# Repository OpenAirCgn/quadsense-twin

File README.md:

# quadsense-twin

This repository contains schematics and board files for an OpenAir
module intended to evaluate the viability of an alternative circuitry to
Alphasense provided ISB (individual support board) for gas sensors.

The board design is based on the original quadsense, with two ISB
mounted sensors replaced by sensors mounted directly on the board. The
support circuitry provided by the ISB boards is integrated directly on
the board.

# Circuitry

Each sensor has four electrodes. The circuit to the left of the sensor
maintains a constant voltage at the counter and reference electrodes.
The circuitry to the right of the electrodes amplifies and filters the
current flowing from the working and auxiliary electrodes.

The concentration being measured is proportional to the difference of
the working electrode exposed to the gas and the unexposed auxiliary
electrode.

The voltage maintained at the referenced and counter electrodes may be offset
by a bias voltage. 

Whether a positive or negative bias voltage is applied voltage
determined by jumper configuration (U1: R16/R17 & R18/R19, U2: R20/R21 &
R22/R23). The value of the bias is determined by a voltage divider (U1:
R12/R13, U2:R14/R15). 

The photograph below highlights an unbiased (U2, top rectangle) and 200mV biased
configuration (U1, bottom rectangle, R12=15k R13=12k). 

# Test boards

| MAC | Sensor U1 | Sensor U2 | ISB 1 | ISB 2 |
|-|-|-|-|-|
| 30:AE:A4:0A:AA:98 | [C0-B4](http://www.alphasense.com/WEB1213/wp-content/uploads/2019/09/CO-B4.pdf) | [OX-B431](http://www.alphasense.com/WEB1213/wp-content/uploads/2019/09/OX-B431.pdf) | CO-B4 | OX-B431 |
| 30:AE:A4:0A:A9:D8 | [NO-B4](http://www.alphasense.com/WEB1213/wp-content/uploads/2019/09/NO-B4.pdf) (biased) | [NO2-B43F](http://www.alphasense.com/WEB1213/wp-content/uploads/2019/09/NO2-B43F.pdf) | NO-B4 | NO2-B43F |

# Sensor Configuration

The following picture and table describe the sensor configuration:

| Name Schematic | ADC Channel | Tag Firehose | Name Firehose | Sensor AA:98 | Sensor A9:D8 |
| -- | - | - | - | - | - |
| U1 | 2 | 0x03 | OA_Alpha_3 | CO-B4 working electrode   | NO-B4 working |
| U1 | 3 | 0x04 | OA_Alpha_4 | CO-B4 auxiliary electrode | NO-B4 AUX |
| U2 | 0 | 0x01 | OA_Alpha_1 | OX-B431 working           | NO2-B43F working |
| U2 | 1 | 0x02 | OA_Alpha_2 | OX-B431 AUX               | NO2-B43F AUX |
| P3 | 4 | 0x05 | OA_Alpha_5 | CO-B4 (ISB) working       | NO-B4 (ISB) working |
| P3 | 5 | 0x06 | OA_Alpha_6 | CO-B4 (ISB) AUX           | NO-B4 (ISB) AUX |
| P4 | 6 | 0x07 | OA_Alpha_7 | OX-B431 (ISB) working     | NO2-B43F (ISB) working |
| P4 | 7 | 0x08 | OA_Alpha_8 | OX-B431 (ISB) AUX         | NO2-B43F (ISB) AUX |

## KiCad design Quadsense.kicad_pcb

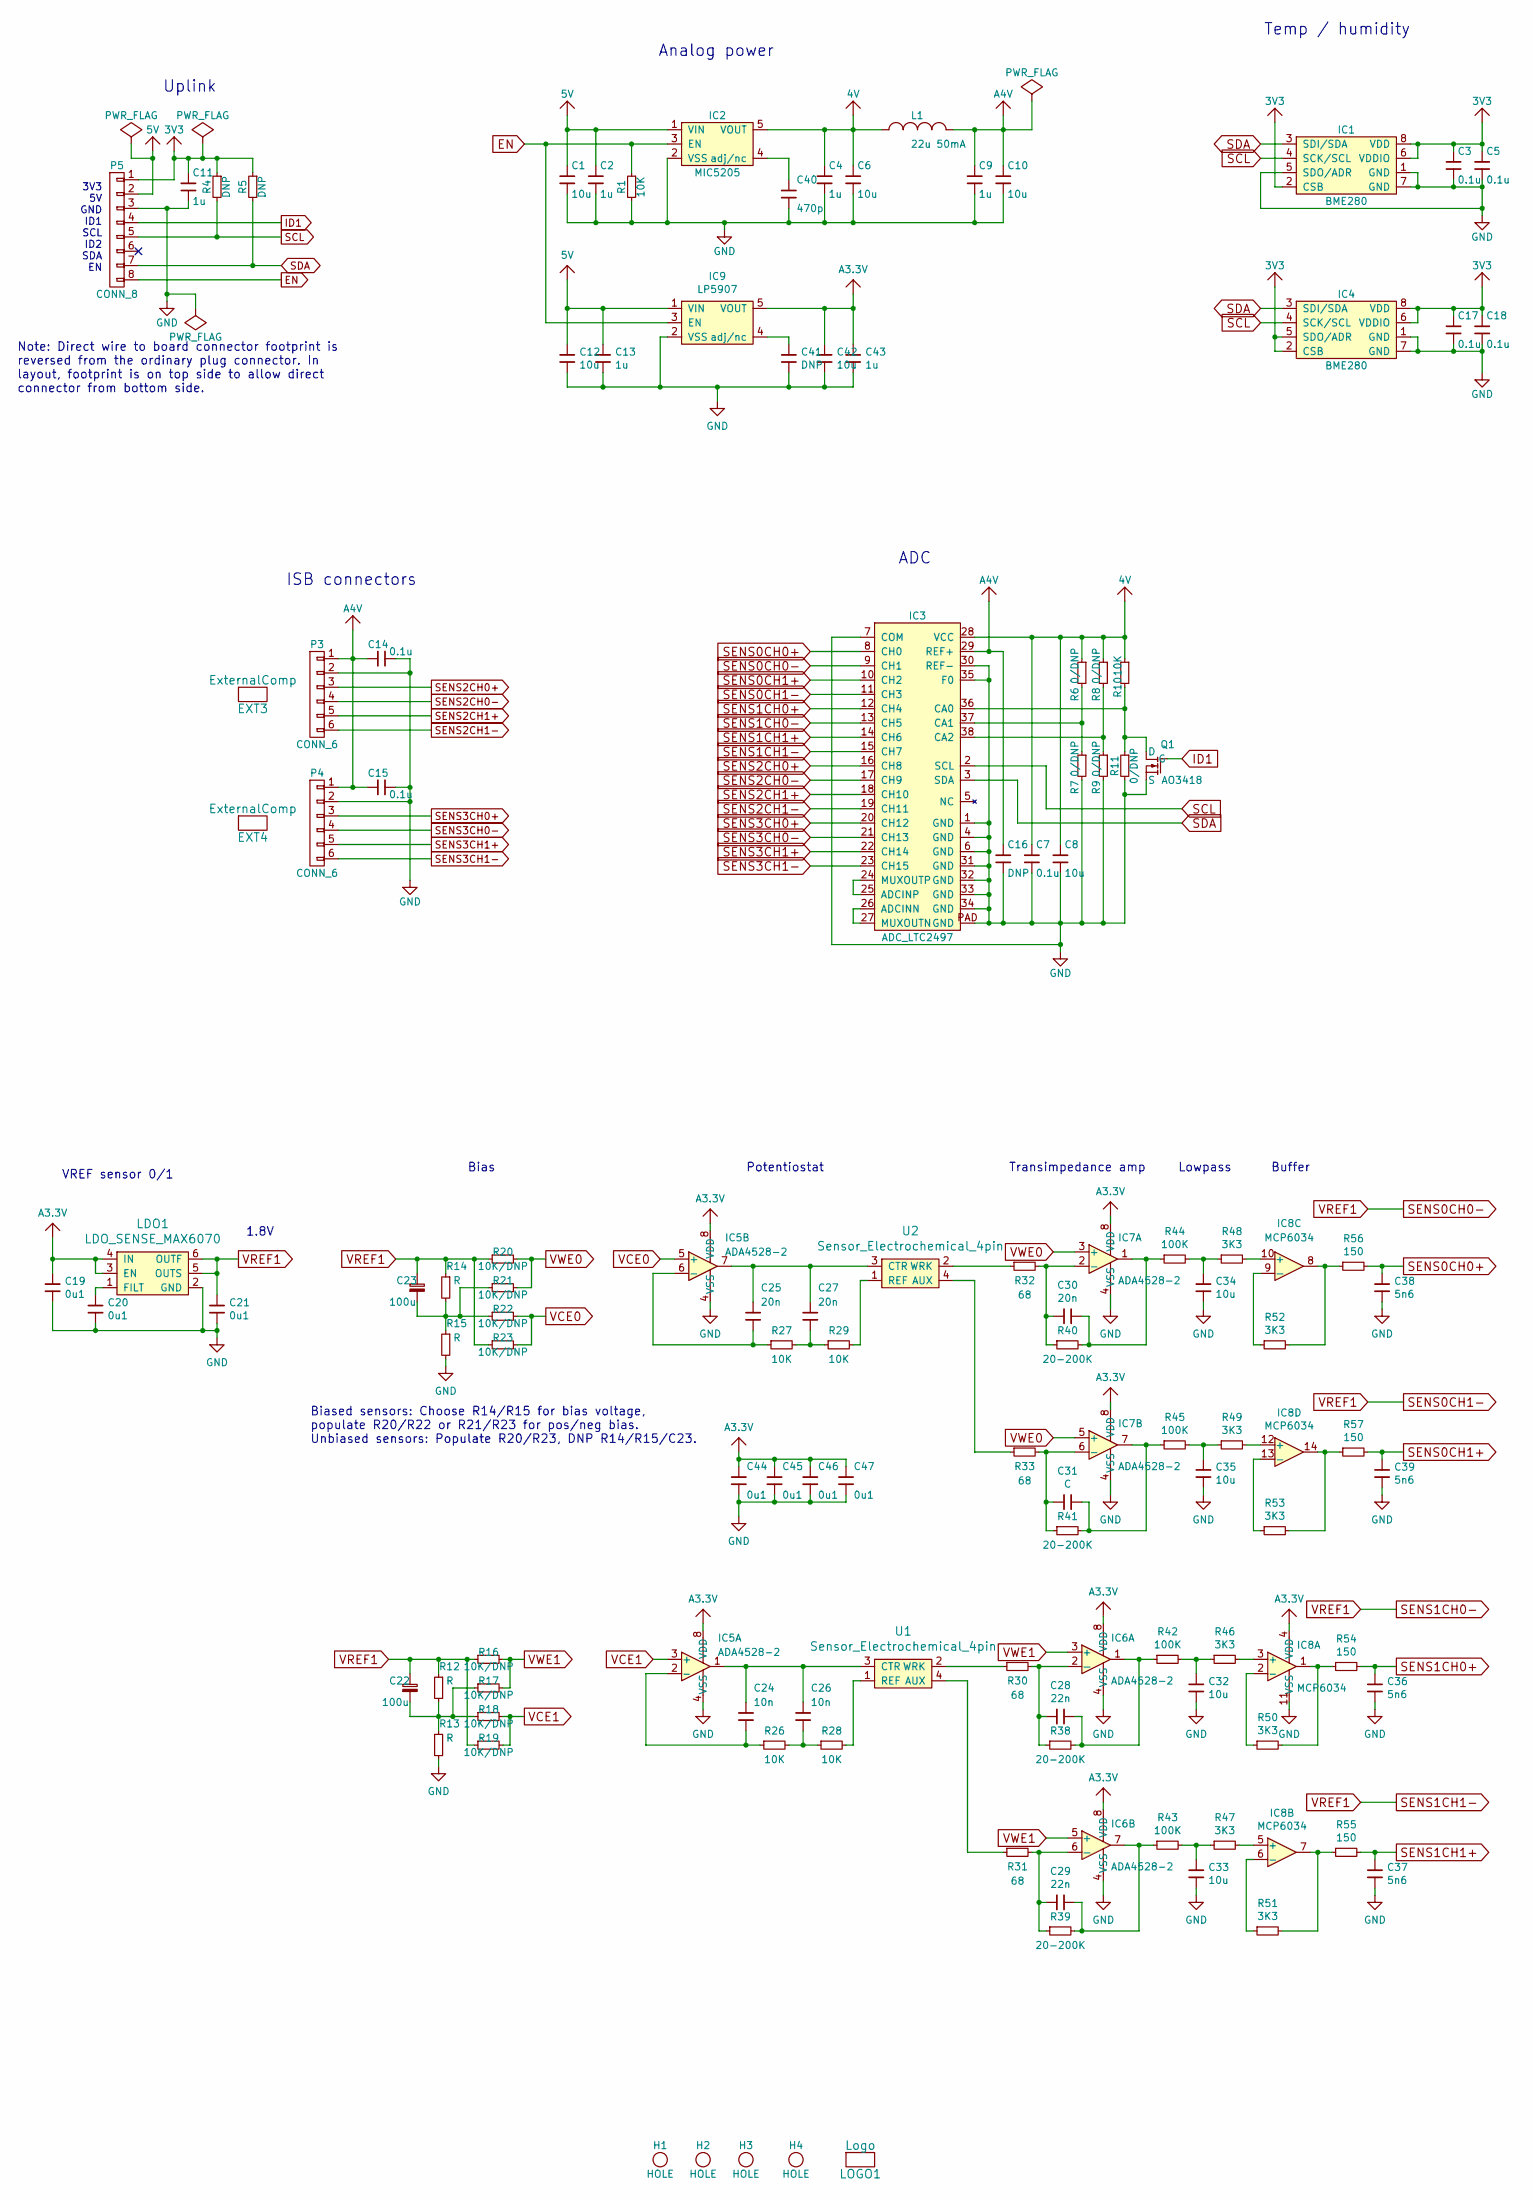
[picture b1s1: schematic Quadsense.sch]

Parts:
C1, C6, C8, C10, C12, C42: 10u; 0603
C2, C4, C9, C11, C13, C43: 1u; 0603
C3, C5, C7, C14, C15, C17, C18: 0.1u; 0603
C16, C41: DNP; 0603
C19, C20, C21, C44, C45, C46, C47: 0u1; 0603
C22, C23: 100u; 1206-POLAR
C24, C26: 10n; 0603
C25, C27, C30: 20n; 0603
C28, C29: 22n; 0603
C31: C; 0603
C32, C33, C34, C35: 10u; 0805
C36, C37, C38, C39: 5n6; 0603
C40: 470p; 0603
EXT3, EXT4: ExternalComp; ALPHASENSE-ISB
H1, H2, H3, H4: HOLE; HOLE-3.2
IC1, IC4: BME280
IC2: MIC5205; SOT23-5
IC3: ADC_LTC2497; QFN-38-12-7-0.5-EP
IC5, IC6, IC7: ADA4528-2; MSOP-8
IC8: MCP6034; TSSOP-14-0.65-4.4
IC9: LP5907; SOT23-5
L1: 22u 50mA; 0805
LDO1: LDO_SENSE_MAX6070; SOT23-6
LOGO1: Logo
P3, P4: CONN_6; HEADER-1x06-1.27-ZZ-POL
P5: CONN_8; HEADER-1x08-1.27-ZZ-POL
Q1: AO3418; SOT23-3
R1, R10, R26, R27, R28, R29: 10K; 0603
R4, R5: DNP; 0603
R6, R7, R8, R9, R11: 0/DNP; 0603
R12, R13, R14, R15: R; 0603
R16, R17, R18, R19, R20, R21, R22, R23: 10K/DNP; 0603
R30, R31, R32, R33: 68; 0603
R38, R39, R40, R41: 20-200K; 0603
R42, R43, R44, R45: 100K; 0603
R46, R47, R48, R49, R50, R51, R52, R53: 3K3; 0603
R54, R55, R56, R57: 150; 0603
U1, U2: Sensor_Electrochemical_4pin; ALPHASENSE_B4

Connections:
4V: C4.1, C6.1, C7.1, C8.1, IC2.5 (VOUT), IC3.28 (VCC), L1.1, R6.1, R8.1, R10.1
A3V3: C19.1, C42.1, C43.1, C44.1, C45.1, C46.1, C47.1, IC5.8 (VDD), IC6.8 (VDD), IC7.8 (VDD), IC8.4 (VDD), IC9.5 (VOUT), LDO1.3 (EN), LDO1.4 (IN)
EN: IC2.3 (EN), IC9.3 (EN), P5.8, R1.1
ID1: P5.4, Q1.1 (G)
unnamed: C20.1, LDO1.1 (FILT)
unnamed: C22.K (-), R12.2, R13.1, R17.1, R18.1
unnamed: C23.K (-), R14.2, R15.1, R21.1, R22.1
unnamed: C24.1, C26.1, IC5.1, U1.3 (CTR)
unnamed: C24.2, IC5.2 (-), R26.1
unnamed: C25.1, C27.1, IC5.7, U2.3 (CTR)
unnamed: C25.2, IC5.6 (-), R27.1
unnamed: C26.2, R26.2, R28.1
unnamed: C27.2, R27.2, R29.1
unnamed: C28.1, IC6.1, R38.2, R42.1
unnamed: C28.2, IC6.2 (-), R30.2, R38.1
unnamed: C29.1, IC6.7, R39.2, R43.1
unnamed: C29.2, IC6.6 (-), R31.2, R39.1
unnamed: C30.1, IC7.1, R40.2, R44.1
unnamed: C30.2, IC7.2 (-), R32.2, R40.1
unnamed: C31.1, IC7.7, R41.2, R45.1
unnamed: C31.2, IC7.6 (-), R33.2, R41.1
unnamed: C32.1, R42.2, R46.1
unnamed: C33.1, R43.2, R47.1
unnamed: C34.1, R44.2, R48.1
unnamed: C35.1, R45.2, R49.1
unnamed: C40.1, IC2.4 (adj/nc)
unnamed: C41.1, IC9.4 (adj/nc)
unnamed: IC3.24 (MUXOUTP), IC3.25 (ADCINP)
unnamed: IC3.26 (ADCINN), IC3.27 (MUXOUTN)
unnamed: IC3.36 (CA0), Q1.3 (D), R10.2, R11.1
unnamed: IC3.37 (CA1), R6.2, R7.1
unnamed: IC3.38 (CA2), R8.2, R9.1
unnamed: IC8.1, R50.2, R54.1
unnamed: IC8.2 (-), R50.1
unnamed: IC8.3 (+), R46.2
unnamed: IC8.5 (+), R47.2
unnamed: IC8.6 (-), R51.1
unnamed: IC8.7, R51.2, R55.1
unnamed: IC8.8, R52.2, R56.1
unnamed: IC8.9 (-), R52.1
unnamed: IC8.10 (+), R48.2
unnamed: IC8.12 (+), R49.2
unnamed: IC8.13 (-), R53.1
unnamed: IC8.14, R53.2, R57.1
unnamed: R28.2, U1.1 (REF)
unnamed: R29.2, U2.1 (REF)
unnamed: R30.1, U1.2 (WRK)
unnamed: R31.1, U1.4 (AUX)
unnamed: R32.1, U2.2 (WRK)
unnamed: R33.1, U2.4 (AUX)
SCL: IC1.4 (SCK/SCL), IC3.2 (SCL), IC4.4 (SCK/SCL), P5.5, R4.2
SDA: IC1.3 (SDI/SDA), IC3.3 (SDA), IC4.3 (SDI/SDA), P5.7, R5.2
SENS0CH0+: C38.1, IC3.8 (CH0), R56.2
SENS0CH0-: C21.1, C22.A (+), C23.A (+), IC3.9 (CH1), IC3.11 (CH3), IC3.13 (CH5), IC3.15 (CH7), LDO1.5 (OUTS), LDO1.6 (OUTF), R12.1, R14.1, R16.1, R19.1, R20.1, R23.1
SENS0CH1+: C39.1, IC3.10 (CH2), R57.2
SENS1CH0+: C36.1, IC3.12 (CH4), R54.2
SENS1CH1+: C37.1, IC3.14 (CH6), R55.2
SENS2CH0+: IC3.16 (CH8), P3.3
SENS2CH0-: IC3.17 (CH9), P3.4
SENS2CH1+: IC3.18 (CH10), P3.5
SENS2CH1-: IC3.19 (CH11), P3.6
SENS3CH0+: IC3.20 (CH12), P4.3
SENS3CH0-: IC3.21 (CH13), P4.4
SENS3CH1+: IC3.22 (CH14), P4.5
SENS3CH1-: IC3.23 (CH15), P4.6
VCE0: IC5.5 (+), R22.2, R23.2
VCE1: IC5.3 (+), R18.2, R19.2
VWE0: IC7.3 (+), IC7.5 (+), R20.2, R21.2
VWE1: IC6.3 (+), IC6.5 (+), R16.2, R17.2

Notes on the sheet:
3V3 5V GND ID1 SCL ID2 SDA EN
Uplink
ISB connectors
Analog power
Temp / humidity
ADC
Note: Direct wire to board connector footprint is reversed from the ordinary plug connector. In layout, footprint is on top side to allow direct connector from bottom side.
VREF sensor 0/1
Bias
Potentiostat
Transimpedance amp
Buffer
Lowpass
Biased sensors: Choose R14/R15 for bias voltage, populate R20/R22 or R21/R23 for pos/neg bias. Unbiased sensors: Populate R20/R23, DNP R14/R15/C23.
1.8V

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
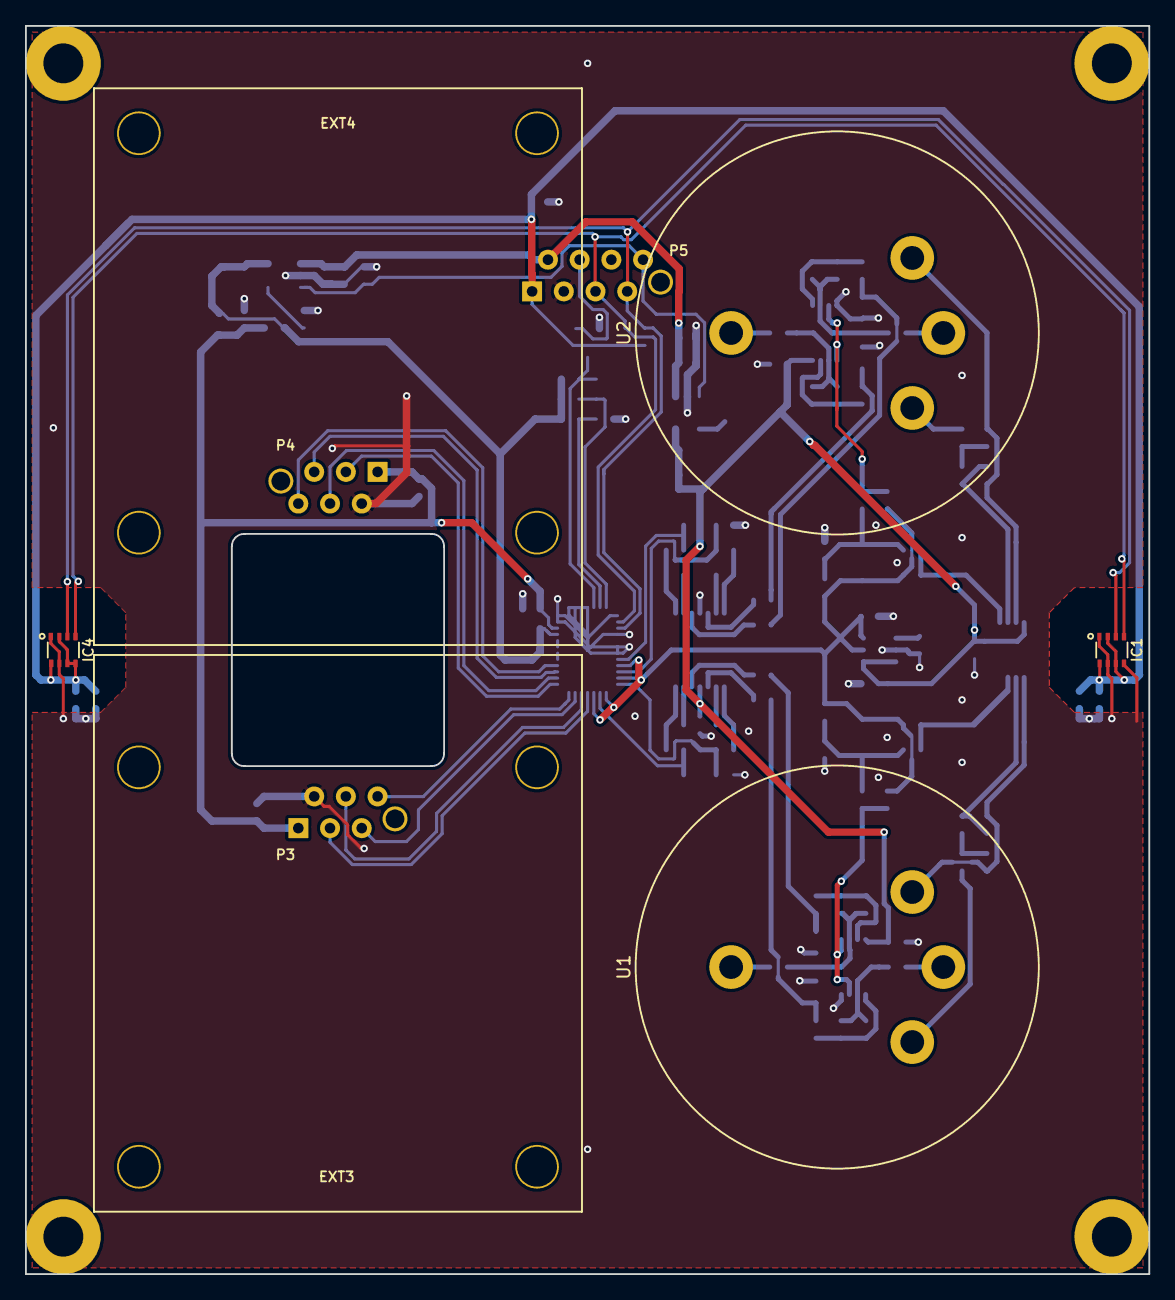
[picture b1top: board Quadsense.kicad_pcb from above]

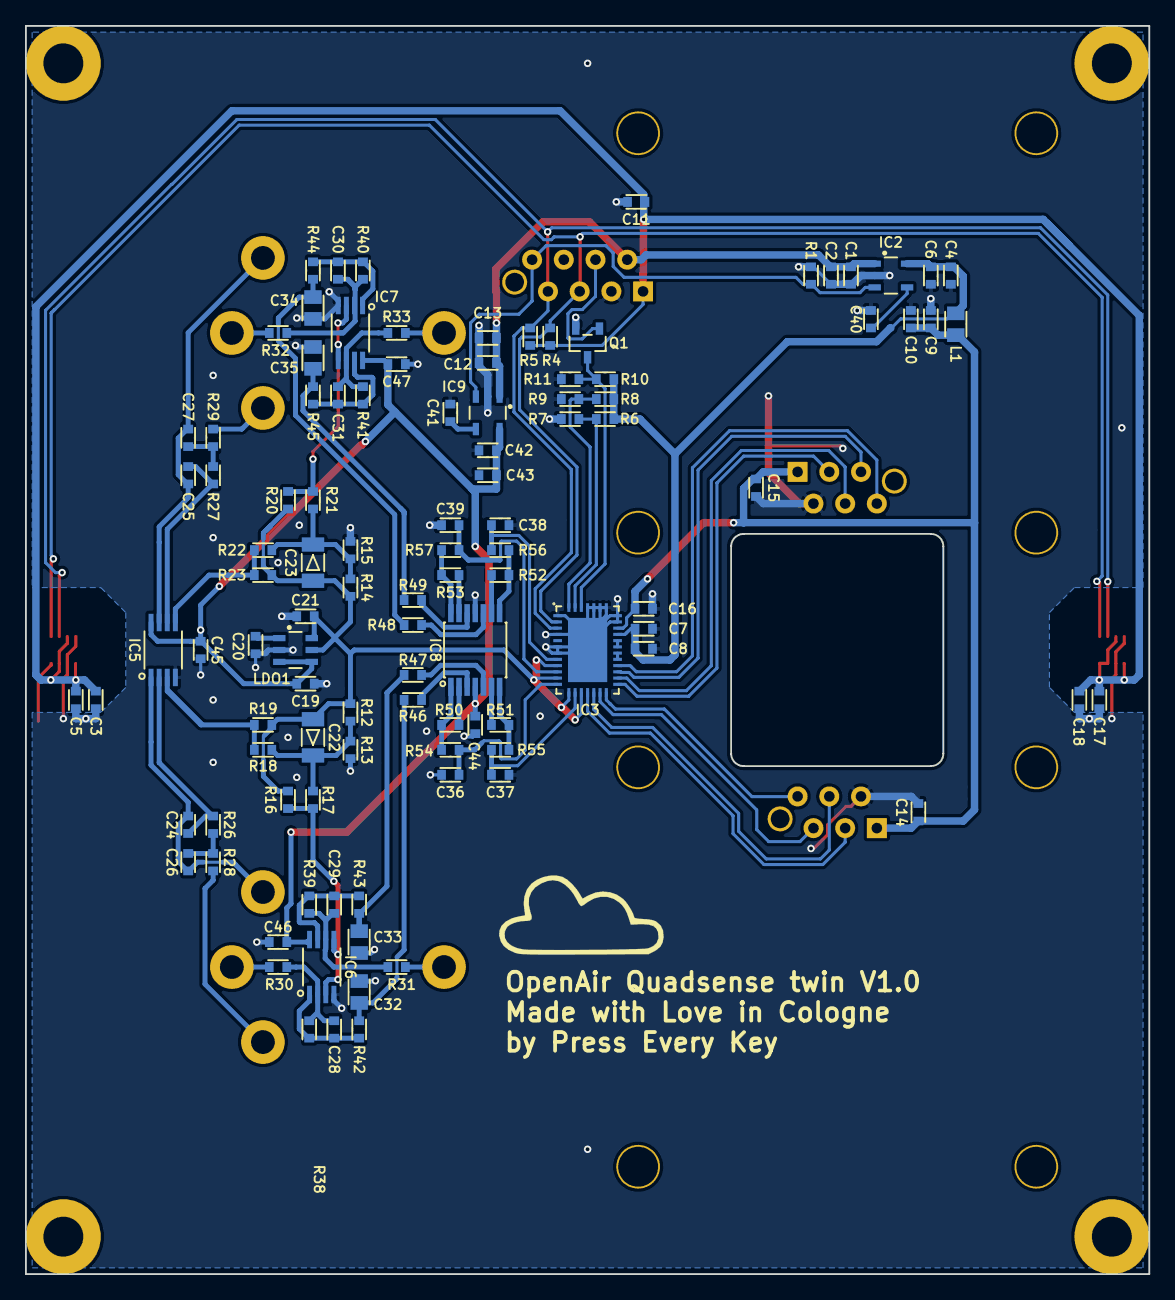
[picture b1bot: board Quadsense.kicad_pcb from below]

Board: 2 copper layers, 90.0 x 100.0 mm, 120 parts (107 on the bottom side), 73 nets.

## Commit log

2020-06-11 Added files
2020-06-11 Schematics cleanup
2020-07-03 Changed version on silkscreen
2020-07-07 gerber files as sent to production 2020-07-06
2020-09-02 ignore bak files
2020-09-02 added rough docs
